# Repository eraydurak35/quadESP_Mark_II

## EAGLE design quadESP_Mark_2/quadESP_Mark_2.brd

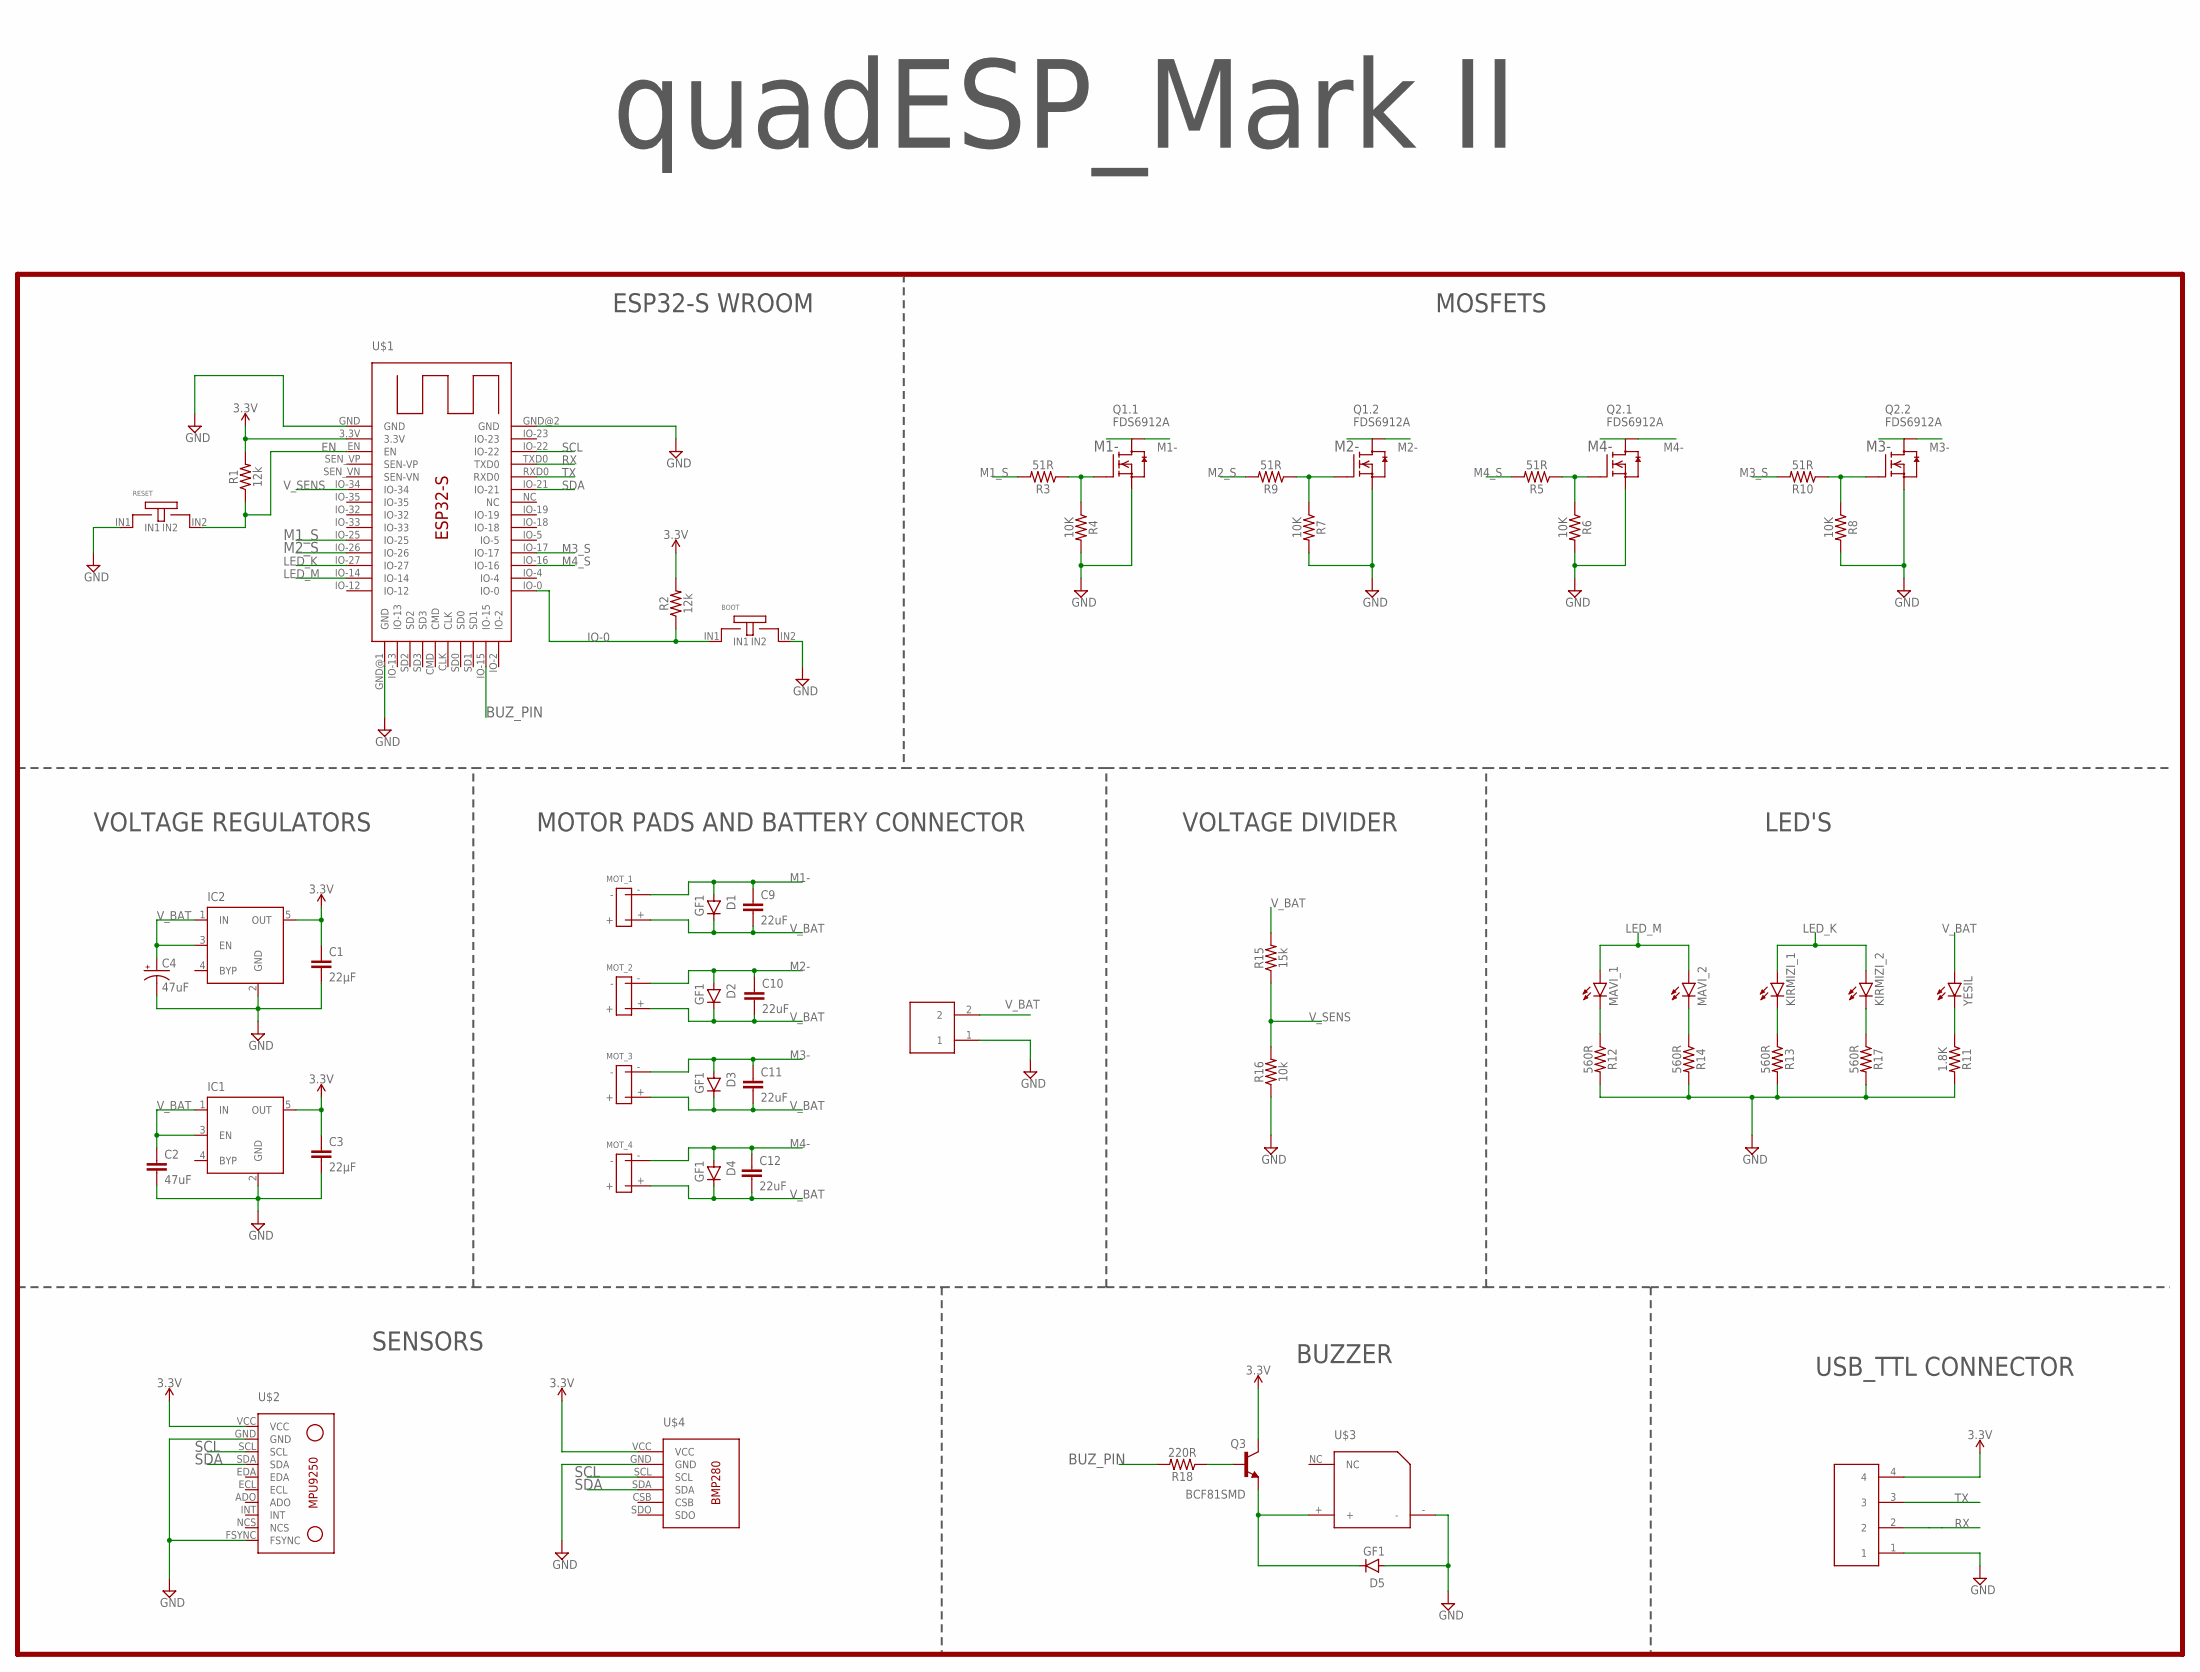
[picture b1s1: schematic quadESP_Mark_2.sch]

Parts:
BOOT: MINI_TIP_SMD_TACT_SWITCH_BUTON
C1, C3: 22µF; 0805
C2: 47uF; 1206
C4: 47uF; EIA3528
C9, C10, C11, C12: 22uF; 1206
D1, D2, D3, D4, D5: GF1; SMA-DO214AC
IC1, IC2: MIC5219XX; SOT23-5
KIRMIZI_1, KIRMIZI_2: LEDCHIP-LED0805; CHIP-LED0805
MAVI_1, MAVI_2: LEDCHIP-LED0805; CHIP-LED0805
MOT_1, MOT_2, MOT_3, MOT_4: 2X_SOLDER_PAD
Q1, Q2: FDS6912A; SO-8
Q3: BCF81SMD; SOT23-BEC
R1, R2: 12k; 0805
R3, R5, R9, R10: 51R; 0805
R4, R6, R7, R8: 10K; 0805
R11: 1.8K; 0805
R12, R13, R14, R17: 560R; 0805
R15: 15k; 0805
R16: 10k; 0805
R18: 220R; 0805
RESET: MINI_TIP_SMD_TACT_SWITCH_BUTON
U$1: ESP32-S
U$2: MPU9250
U$3: PASIVE_BUZZER_5MM_X_5MM_20MM
U$4: BMP280
U$5: 2_PIN_TUNIC
U$6: 4_PIN_TUNIC
YESIL: LEDCHIP-LED0805; CHIP-LED0805

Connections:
3.3V: C1.1, C3.1, IC1.5 (OUT), IC2.5 (OUT), Q3.C, R1.2, R2.2, U$1.3.3V, U$2.VCC, U$4.VCC, U$6.4
BUZ_PIN: R18.2, U$1.IO-15
EN: R1.1, RESET.IN2, U$1.EN
GND: BOOT.IN2, C1.2, C2.2, C3.2, C4.C (-), D5.A, IC1.2 (GND), IC2.2 (GND), Q1.1 (S), Q1.3 (S), Q2.1 (S), Q2.3 (S), R4.2, R6.2, R7.2, R8.2, R11.2, R12.2, R13.2, R14.2, R16.1, R17.2, RESET.IN1, U$1.GND, U$1.GND@1 (GND), U$1.GND@2 (GND), U$2.FSYNC, U$2.GND, U$3.-, U$4.GND, U$5.1, U$6.1
IO-0: BOOT.IN1, R2.1, U$1.IO-0
LED_K: KIRMIZI_1.A, KIRMIZI_2.A, U$1.IO-27
LED_M: MAVI_1.A, MAVI_2.A, U$1.IO-14
M1-: C9.1, D1.A, MOT_1.-, Q1.5 (D), Q1.6 (D)
M1_S: R3.2, U$1.IO-25
M2-: C10.1, D2.A, MOT_2.-, Q1.7 (D), Q1.8 (D)
M2_S: R9.2, U$1.IO-26
M3-: C11.1, D3.A, MOT_3.-, Q2.7 (D), Q2.8 (D)
M3_S: R10.2, U$1.IO-17
M4-: C12.1, D4.A, MOT_4.-, Q2.5 (D), Q2.6 (D)
M4_S: R5.2, U$1.IO-16
unnamed: MAVI_2.C, R14.1
unnamed: KIRMIZI_1.C, R13.1
unnamed: KIRMIZI_2.C, R17.1
unnamed: R11.1, YESIL.C
unnamed: MAVI_1.C, R12.1
unnamed: Q1.4 (G), R3.1, R4.1
unnamed: Q1.2 (G), R7.1, R9.1
unnamed: Q2.4 (G), R5.1, R6.1
unnamed: Q2.2 (G), R8.1, R10.1
unnamed: Q3.B, R18.1
unnamed: D5.K (C), Q3.E, U$3.+
RX: U$1.TXD0, U$6.2
SCL: U$1.IO-22, U$2.SCL, U$4.SCL
SDA: U$1.IO-21, U$2.SDA, U$4.SDA
TX: U$1.RXD0, U$6.3
V_BAT: C2.1, C4.A (+), C9.2, C10.2, C11.2, C12.2, D1.K (C), D2.K (C), D3.K (C), D4.K (C), IC1.1 (IN), IC1.3 (EN), IC2.1 (IN), IC2.3 (EN), MOT_1.+, MOT_2.+, MOT_3.+, MOT_4.+, R15.2, U$5.2, YESIL.A
V_SENS: R15.1, R16.2, U$1.IO-34

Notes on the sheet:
ESP32-S WROOM
MOSFETS
LED'S
VOLTAGE DIVIDER
MOTOR PADS AND BATTERY CONNECTOR
VOLTAGE REGULATORS
SENSORS
USB_TTL CONNECTOR
BUZZER
quadESP_Mark II

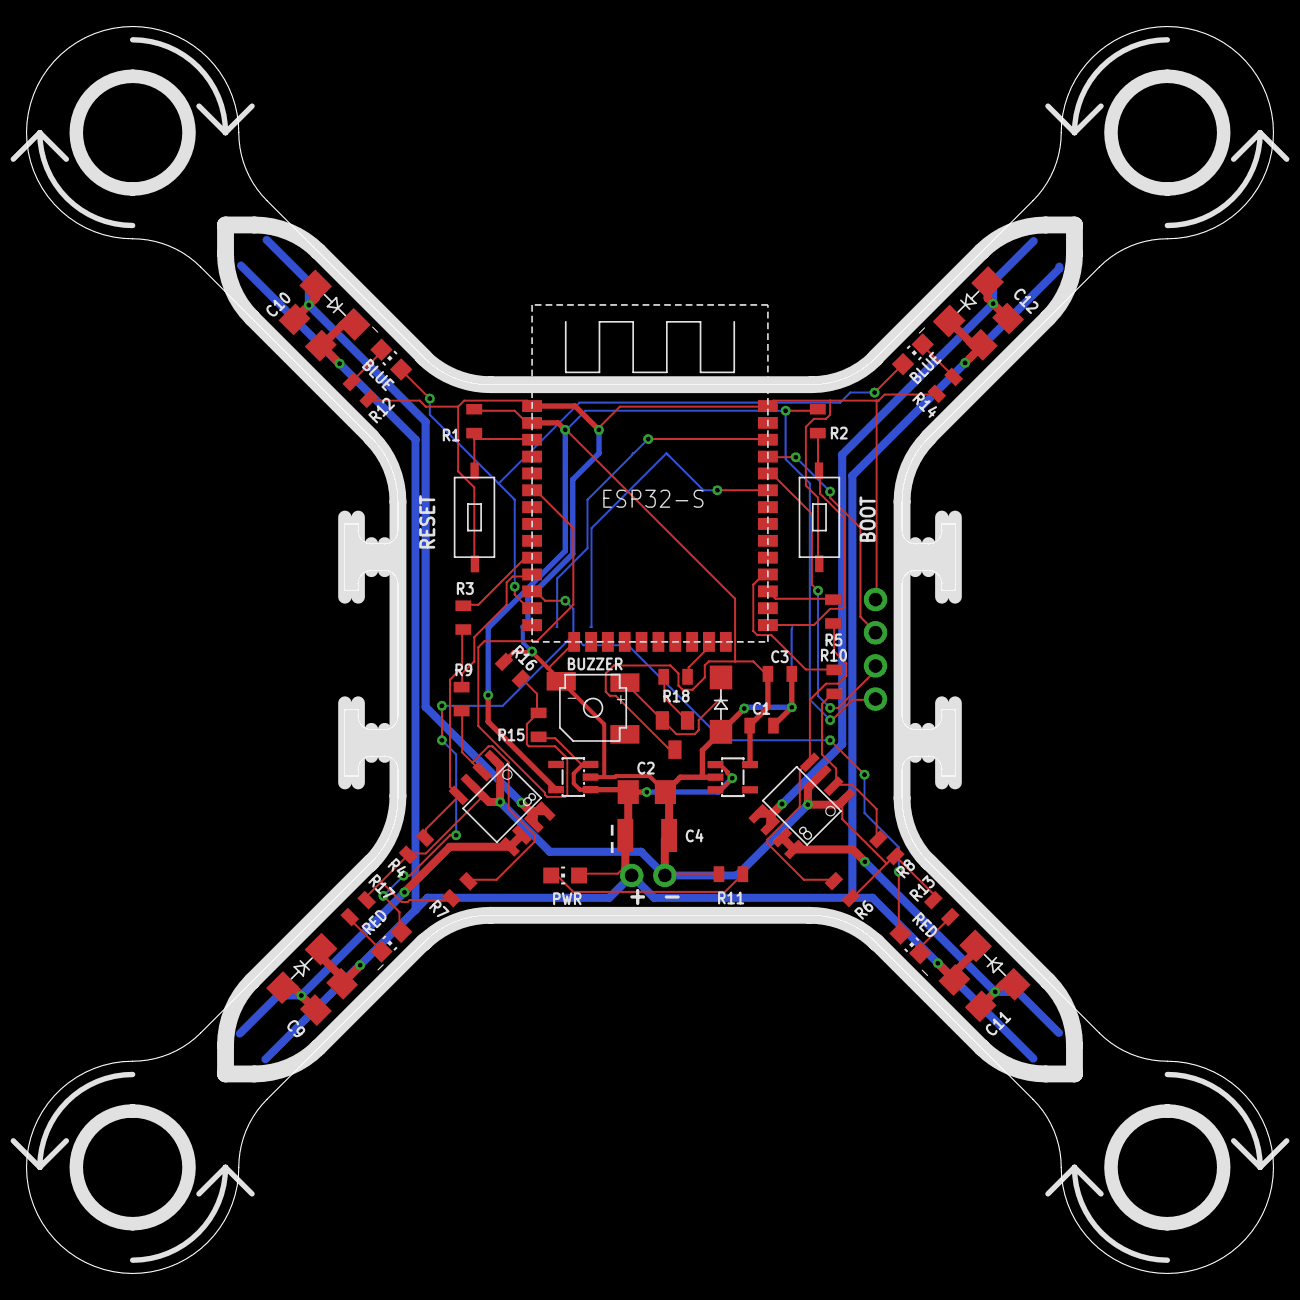
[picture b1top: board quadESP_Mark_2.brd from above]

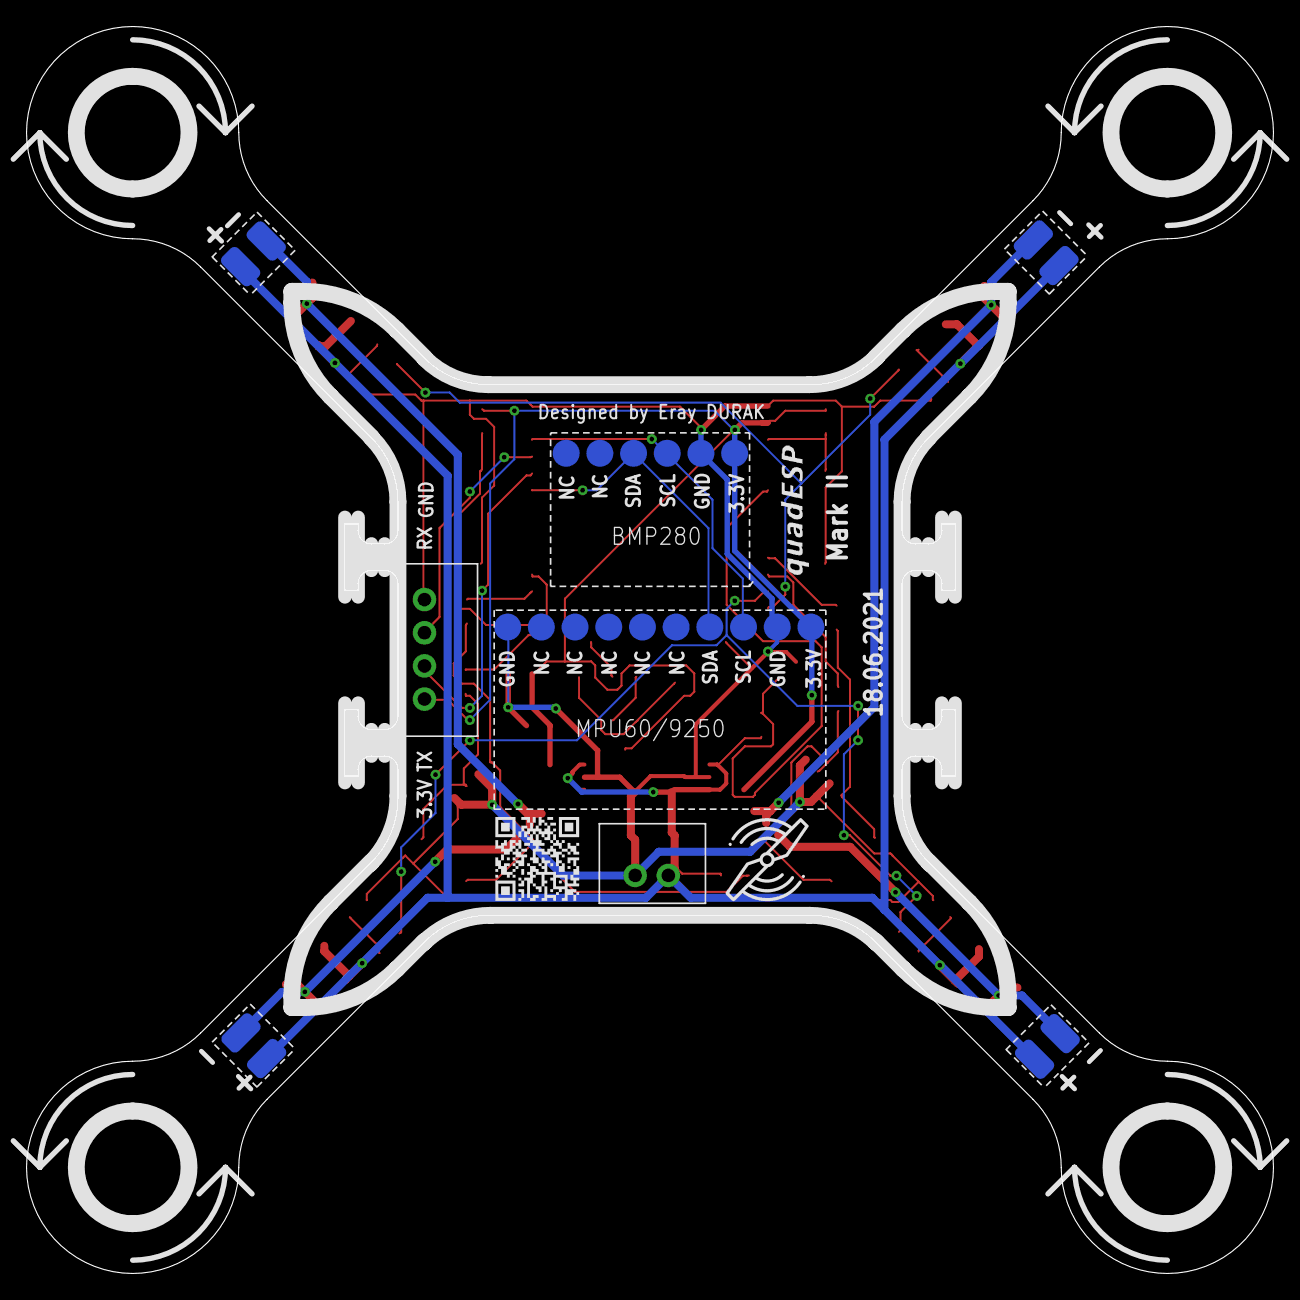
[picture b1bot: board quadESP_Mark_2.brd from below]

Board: 2 copper layers, 94.0 x 94.0 mm, 53 parts (6 on the bottom side), 32 nets.

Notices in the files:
parts and their libraries:
SparkFun-Capacitors: Licensing: Creative Commons ShareAlike 4.0 International - https://creativecommons.org/licenses/by-sa/4.0
m-pad-2.1: License : GNU General Public License version 2 (see bottom)
